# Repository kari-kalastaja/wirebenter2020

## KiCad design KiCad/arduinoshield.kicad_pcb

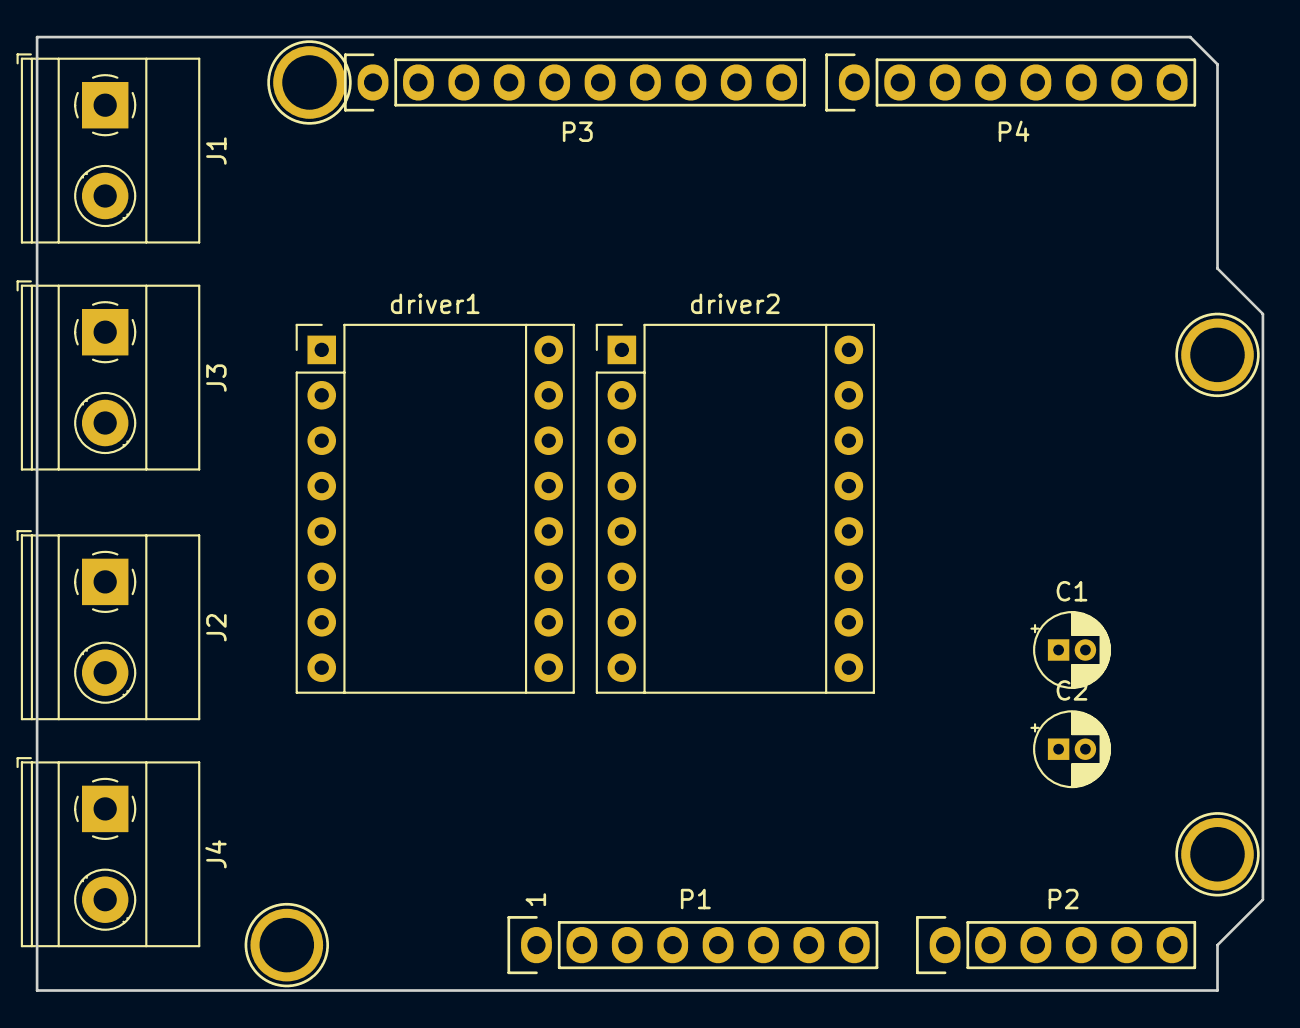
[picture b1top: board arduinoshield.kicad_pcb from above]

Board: 2 copper layers, 68.6 x 53.3 mm, 16 parts (0 on the bottom side), 17 nets, no tracks yet.

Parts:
C1, C2: CP; CP_Radial_D4.0mm_P1.50mm
J1, J2, J3, J4: Screw_Terminal_01x02; TerminalBlock_Phoenix_MKDS-1,5-2-5.08_1x02_P5.08mm_Horizont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
P1: Power; Socket_Strip_Arduino_1x08
P2: Analog; Socket_Strip_Arduino_1x06
P3: Digital; Socket_Strip_Arduino_1x10
P4: Digital; Socket_Strip_Arduino_1x08
P5, P6, P7, P8: CONN_01X01; Arduino_1pin
driver1, driver2: Pololu_Breakout_DRV8825; Pololu_Breakout-16_15.2x20.3mm

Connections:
+5V: P1.5, driver1.13, driver1.14, driver2.13, driver2.14
/0(Rx): P4.8, driver2.15
/1(Tx): P4.7, driver2.16
/2: P4.6, driver1.15
/3(**): P4.5, driver1.16
/A4(SDA): P2.5, P3.2
/A5(SCL): P2.6, P3.1
/Vin: C1.1, C2.1, P1.8, driver1.8, driver2.8
GND: C1.2, C2.2, P1.6, P1.7, P3.4, driver1.1, driver1.7, driver2.1, driver2.7
unnamed: J1.1, driver1.4
unnamed: J1.2, driver1.3
unnamed: J2.1, driver2.5
unnamed: J2.2, driver2.6
unnamed: J3.1, driver1.5
unnamed: J3.2, driver1.6
unnamed: J4.1, driver2.4
unnamed: J4.2, driver2.3

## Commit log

2020-12-28 santeri
2020-12-28 jotain
2021-01-10 kicad
2021-01-10 3d models
